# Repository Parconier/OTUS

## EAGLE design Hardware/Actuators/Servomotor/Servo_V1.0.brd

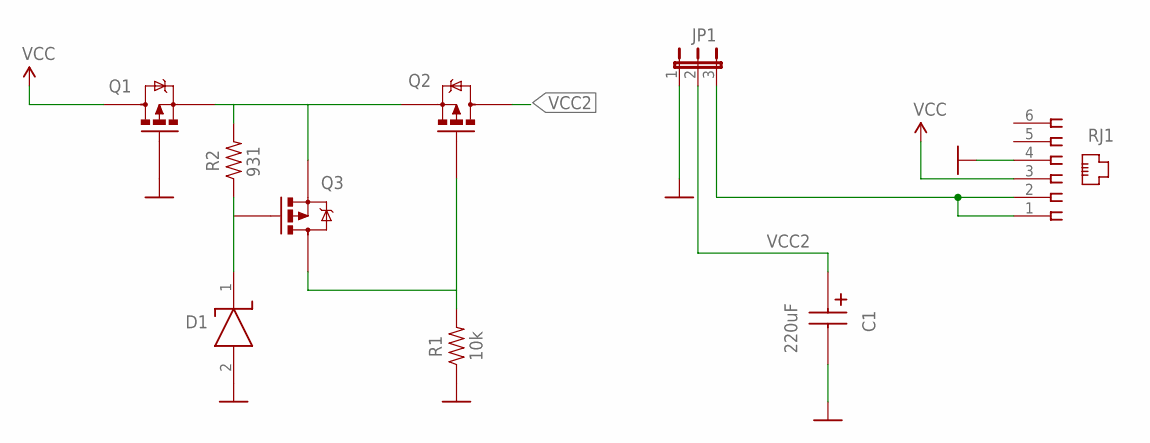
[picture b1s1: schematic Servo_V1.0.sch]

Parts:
C1: 220uF; CAPPRD200W80D500H1100; MPN 227CKS010M
D1: BZT52C5V1-7-F; SOD3716X145N; MPN BZT52C5V1-7-F
JP1: JP2E; JP2; MPN 5-146284-3
Q1, Q2, Q3: IRLML2244TRPBF; SOT95P237X112-3N; MANUFACTURER_PART_NUMBER IRLML2244TRPBF
R1: 10k; RESC1005X35; MPN RC0402JR-7W10KL
R2: 931; RESC1005X35; MPN RC0402FR-07931RL
RJ1: 615006138421; MPN 615006138421

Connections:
GND: C1.2 (-), D1.2 (A), JP1.1, Q1.1 (G), R1.1, RJ1.4
unnamed: Q1.2 (S), Q2.2 (S), Q3.2 (S), R2.2
unnamed: Q2.1 (G), Q3.3 (D), R1.2
unnamed: JP1.3, RJ1.1, RJ1.2
unnamed: D1.1 (K), Q3.1 (G), R2.1
VCC: Q1.3 (D), RJ1.3
VCC2: C1.1 (+), JP1.2, Q2.3 (D)

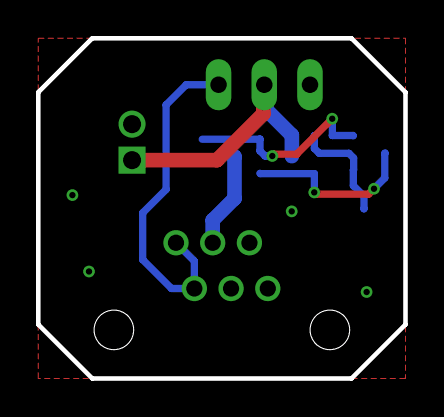
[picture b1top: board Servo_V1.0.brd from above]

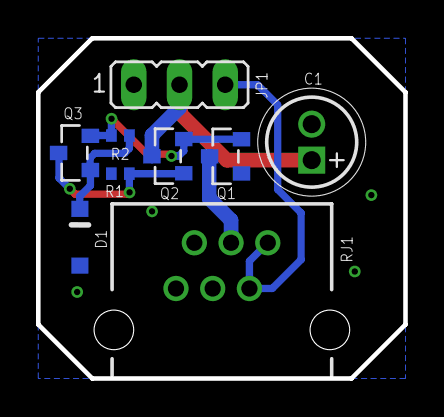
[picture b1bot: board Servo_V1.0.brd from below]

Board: 2 copper layers, 20.4 x 18.9 mm, 9 parts (9 on the bottom side), 7 nets.

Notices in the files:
parts and their libraries:
SparkFun-Aesthetics: Licensing: Creative Commons ShareAlike 4.0 International - https://creativecommons.org/licenses/by-sa/4.0
MyFrames: Released under the Creative Commons
MyFrames: https://creativecommons.org/licenses/by-sa/4.0
